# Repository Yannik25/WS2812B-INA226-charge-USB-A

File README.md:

# WS2812B-INA226-charge-USB-A
Measure current of connected device and control WS2812B LEDs

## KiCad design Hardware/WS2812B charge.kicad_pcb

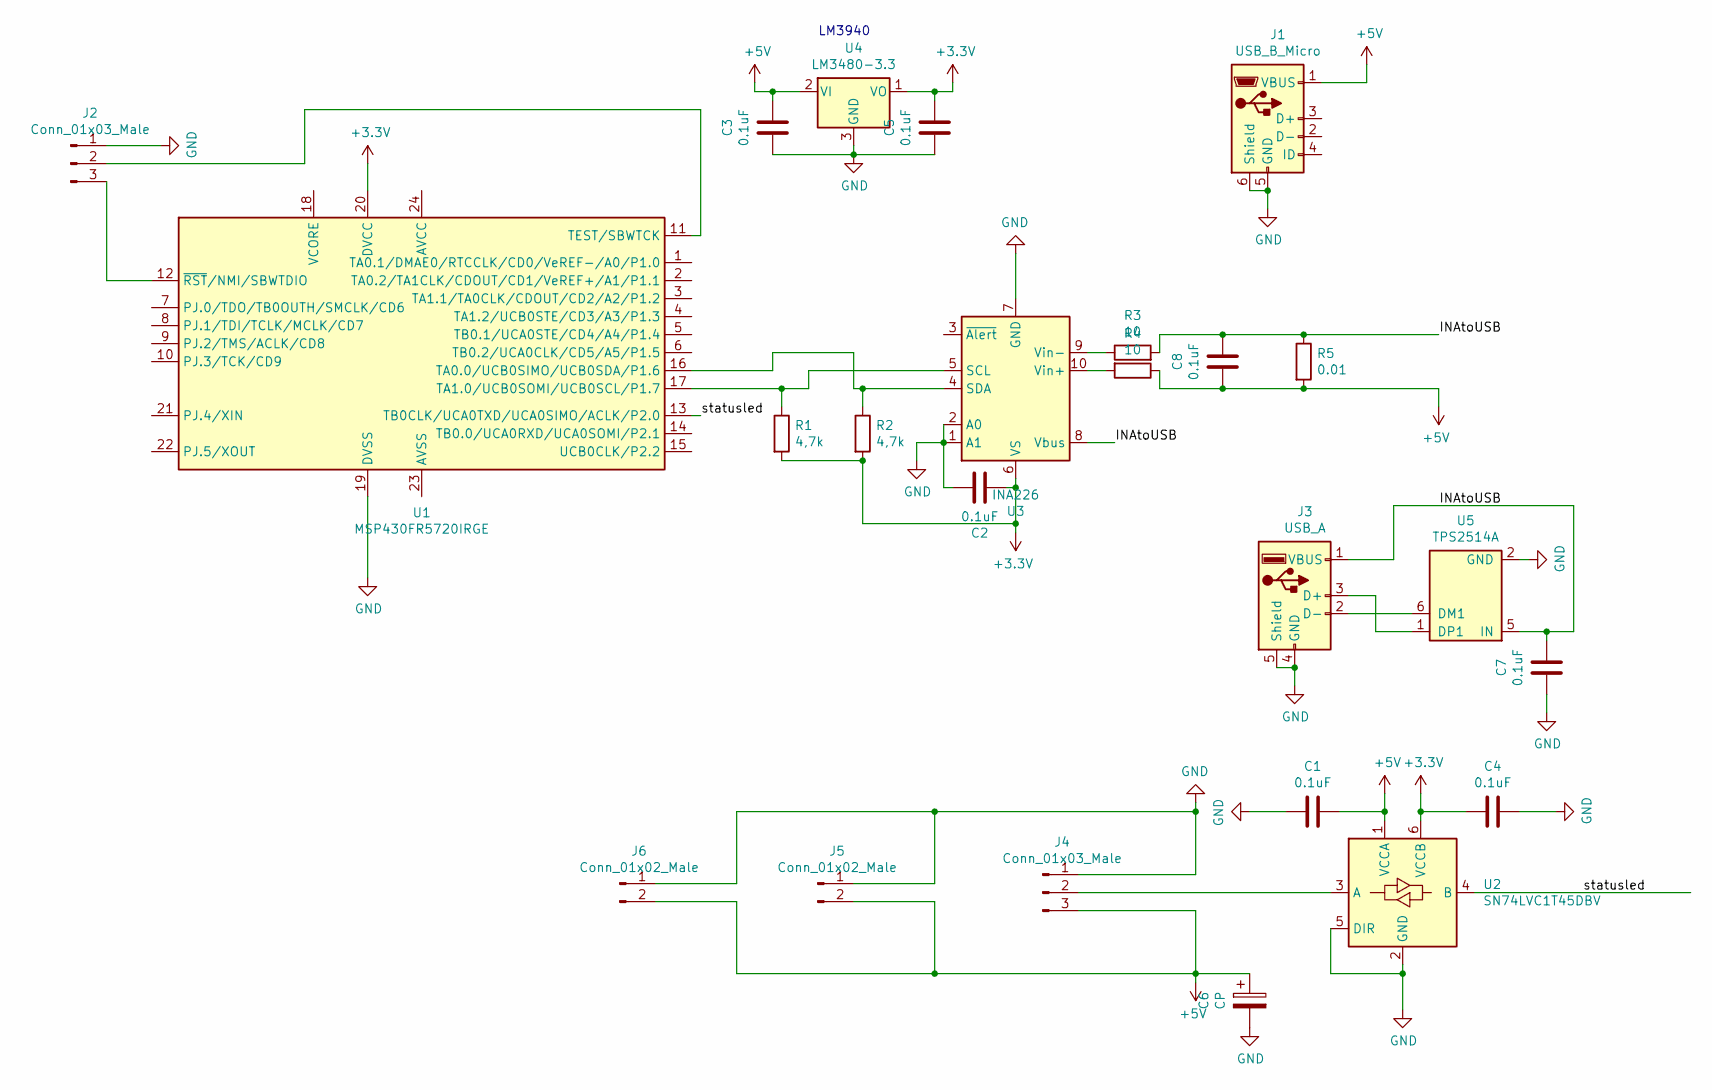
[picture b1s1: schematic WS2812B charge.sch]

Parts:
C1, C2, C3, C4, C5, C7, C8: 0.1uF; C_0402_1005Metric
C6: CP; C_Radial_D5.0mm_H7.0mm_P2.00mm
J1: USB_B_Micro; USB_Micro-B_Molex_47346-0001
J2, J4: Conn_01x03_Male; PinHeader_1x03_P2.54mm_Vertical
J3: USB_A; USB_A_Stewart_SS-52100-001_Horizontal
J5, J6: Conn_01x02_Male; PinHeader_1x02_P2.54mm_Vertical
R1, R2: 4,7k; R_0402_1005Metric
R3, R4: 10; R_0402_1005Metric
R5: 0.01; R_0805_2012Metric
U1: MSP430FR5720IRGE; Texas_S-PVQFN-N24_EP2.1x2.1mm
U2: SN74LVC1T45DBV; SOT-23-6
U3: INA226; VSSOP-10_3x3mm_P0.5mm
U4: LM3480-3.3; SOT-23
U5: TPS2514A; SOT-23-6

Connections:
+3V3: C2.2, C4.2, C5.1, R1.2, R2.2, U1.20 (DVCC), U2.6 (VCCB), U3.6 (VS), U4.1 (VO)
+5V: C1.1, C3.1, C6.1, C8.2, J1.1 (VBUS), J4.3, J5.2, J6.2, R4.1, R5.2, U2.1 (VCCA), U4.2 (VI)
/INAtoUSB: C7.1, C8.1, J3.1 (VBUS), R3.2, R5.1, U3.8 (Vbus), U5.5 (IN)
/statusled: U1.13 (TB0CLK/UCA0TXD/UCA0SIMO/ACLK/P2.0), U2.4 (B)
GND: C1.2, C2.1, C3.2, C4.1, C5.2, C6.2, C7.2, J1.5 (GND), J1.6 (Shield), J2.1, J3.4 (GND), J3.5 (Shield), J4.1, J5.1, J6.1, U1.19 (DVSS), U2.2 (GND), U2.5 (DIR), U3.1 (A1), U3.2 (A0), U3.7 (GND), U4.3 (GND), U5.2 (GND)
unnamed: J2.2, U1.11 (TEST/SBWTCK)
unnamed: J2.3, U1.12 (~RST~/NMI/SBWTDIO)
unnamed: J3.2 (D-), U5.6 (DM1)
unnamed: J3.3 (D+), U5.1 (DP1)
unnamed: J4.2, U2.3 (A)
unnamed: R1.1, U1.17 (TA1.0/UCB0SOMI/UCB0SCL/P1.7), U3.5 (SCL)
unnamed: R2.1, U1.16 (TA0.0/UCB0SIMO/UCB0SDA/P1.6), U3.4 (SDA)
unnamed: R3.1, U3.9 (Vin-)
unnamed: R4.2, U3.10 (Vin+)

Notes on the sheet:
LM3940

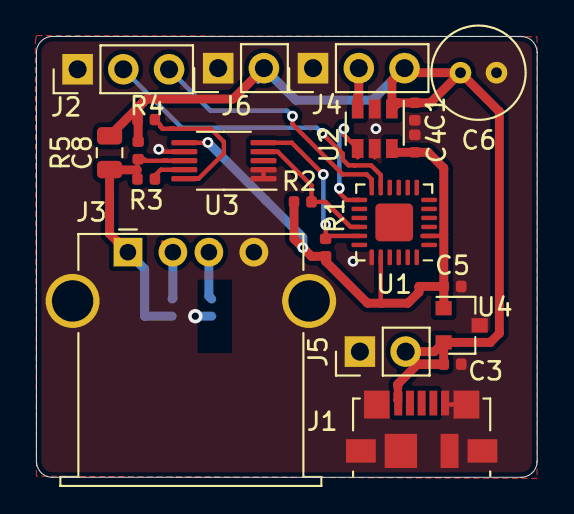
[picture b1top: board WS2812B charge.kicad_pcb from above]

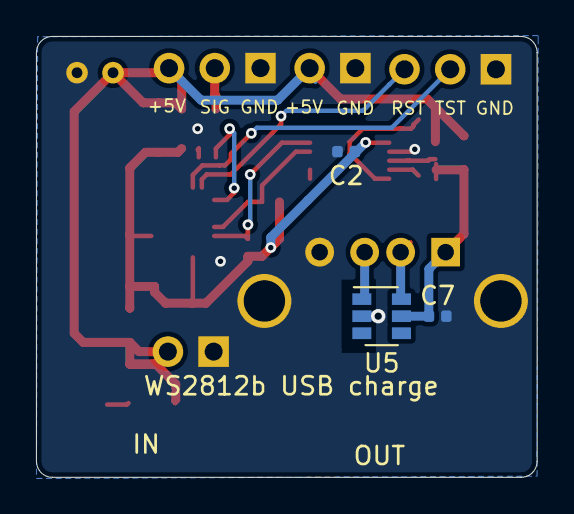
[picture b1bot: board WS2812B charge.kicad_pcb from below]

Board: 2 copper layers, 27.8 x 24.5 mm, 24 parts (3 on the bottom side), 14 nets.

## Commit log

2021-10-07 add Hardware
2021-10-07 add basic code, read ina works, ws2812 can be controlled, no combination between ina and leds yet
